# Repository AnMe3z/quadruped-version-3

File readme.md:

# Мобилен робот с безжично управление
## _MECHKA v3_

Целта на дипломната работа е да се създаде четирикрак робот с безжично управление.

Дипломант:     Андрей Методиев Ежков 12Г Випуск 2024

Ръководител: Владимир Иванов

В текущата репозитория е разделена на:

- hardware/ - четежи, CAD файлове и рендери
- software/ - сорс код на изработката

## hardware/

Тук се намират всички чертежи по корпуса, CAD файлове, рендери и файловете за платката:

- body/
- leg/
- motor/
- schematics/

Както и 3Д рендер на цялостния робот

## software/

Тук се намира сорс кода на проекта

- main/
- main.c
- control-app/
- app.c

main.c е софтуерът за микроконтролера. Инструкции за флашване:

```sh
cd software/main/build
chmod +x upload.sh
./upload.sh
```

app.py е GUI-то за контрол върху робота. Инструкции:

```sh
cd software/control-app/
source venv/bin/activate
python3 app.py
```

## License

Copyright 2023-2024 All rights reserved
Андрей Ежков си запазва всички права

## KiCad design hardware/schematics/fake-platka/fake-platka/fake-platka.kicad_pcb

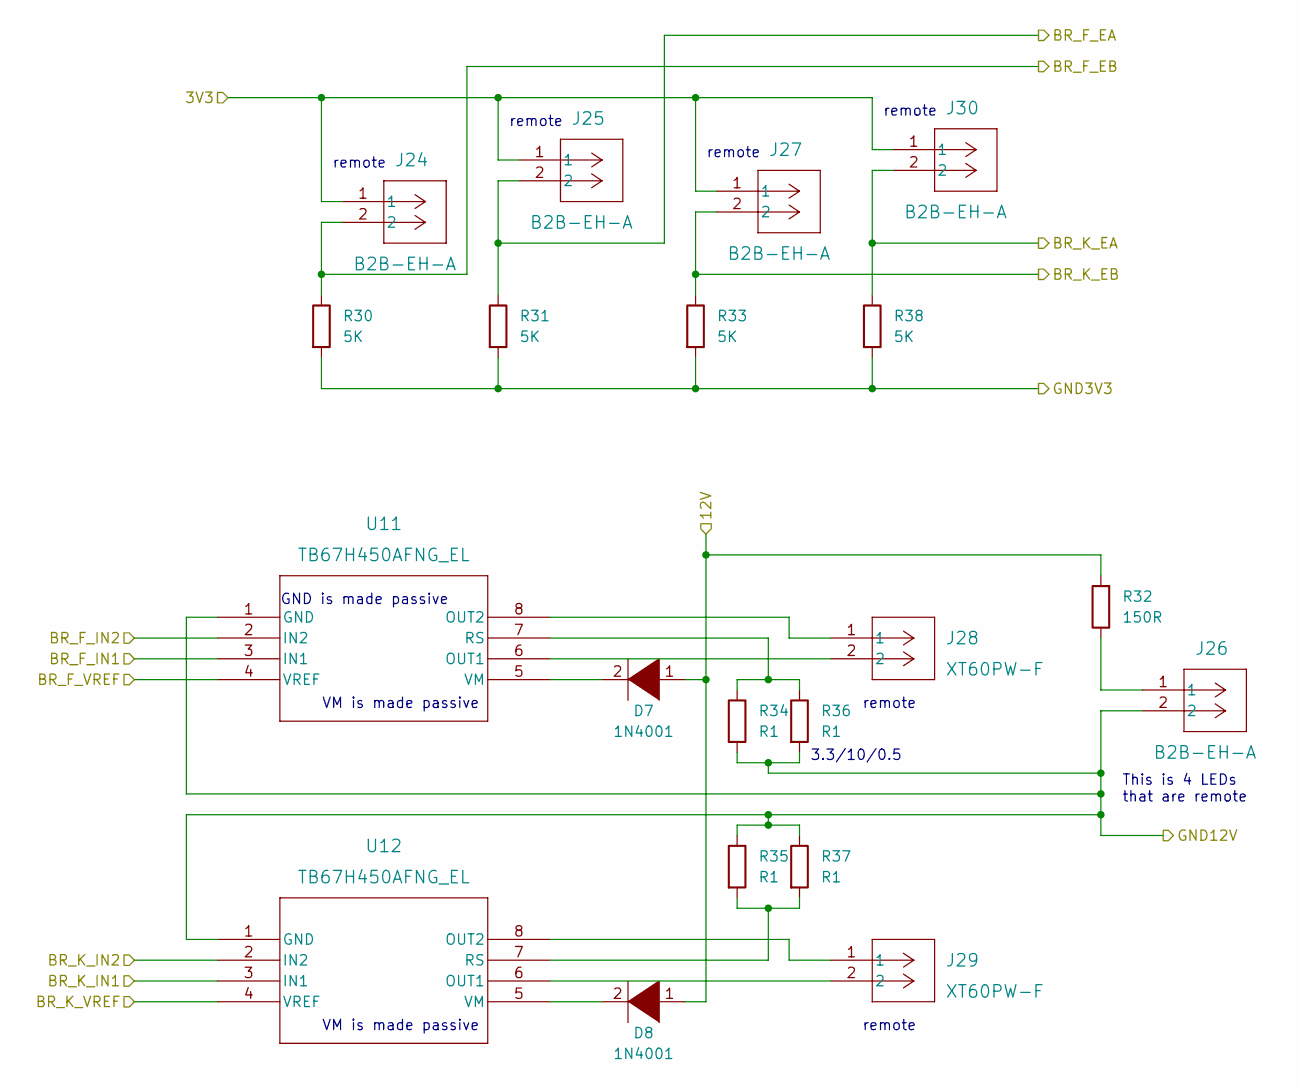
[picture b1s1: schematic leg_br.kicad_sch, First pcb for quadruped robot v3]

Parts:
D7, D8: 1N4001; D_DO-41_SOD81_P7.62mm_Horizontal
J24, J25, J26, J27, J30: B2B-EH-A; CONN_B2B-EH-A LFSN_JST
J28, J29: XT60PW-F; CONN_XT60PW-F_AMA
R30, R31, R33, R38: 5K; R_Axial_DIN0207_L6.3mm_D2.5mm_P10.16mm_Horizontal
R32: 150R; R_Axial_DIN0207_L6.3mm_D2.5mm_P10.16mm_Horizontal
R34, R35, R36, R37: R1; R_Axial_DIN0207_L6.3mm_D2.5mm_P10.16mm_Horizontal
U11, U12: TB67H450AFNG_EL; P-HSOP8-0405-1.27-002_TOS

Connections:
/Left Controller /3V3: J24.1, J25.1, J27.1, J30.1; also elsewhere on the board
/Left Controller /GND3V3: R30.2, R31.2, R33.2, R38.2; also elsewhere on the board
/Leg Back Left/12V: D7.1 (K), D8.1 (K), R32.2; also elsewhere on the board
/Leg Back Right/BR_F_EA: J25.2, R31.1; also elsewhere on the board
/Leg Back Right/BR_F_EB: J24.2, R30.1; also elsewhere on the board
/Leg Back Right/BR_F_IN1: U11.3 (IN1); also elsewhere on the board
/Leg Back Right/BR_F_IN2: U11.2 (IN2); also elsewhere on the board
/Leg Back Right/BR_F_VREF: U11.4 (VREF), U12.4 (VREF); also elsewhere on the board
/Leg Back Right/BR_K_EA: J30.2, R38.1; also elsewhere on the board
/Leg Back Right/BR_K_EB: J27.2, R33.1; also elsewhere on the board
/Leg Back Right/BR_K_IN1: U12.3 (IN1); also elsewhere on the board
/Leg Back Right/BR_K_IN2: U12.2 (IN2); also elsewhere on the board
/Leg Back Right/GND12V: J26.2, R34.2, R35.1, R36.2, R37.1, U11.1 (GND), U12.1 (GND); also elsewhere on the board
unnamed: D7.2 (A), U11.5 (VM)
unnamed: D8.2 (A), U12.5 (VM)
unnamed: J26.1, R32.1
unnamed: J28.1, U11.8 (OUT2)
unnamed: J28.2, U11.6 (OUT1)
unnamed: J29.1, U12.8 (OUT2)
unnamed: J29.2, U12.6 (OUT1)
unnamed: R34.1, R36.1, U11.7 (RS)
unnamed: R35.2, R37.2, U12.7 (RS)

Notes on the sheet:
GND is made passive
remote
This is 4 LEDs that are remote
VM is made passive
3.3/10/0.5

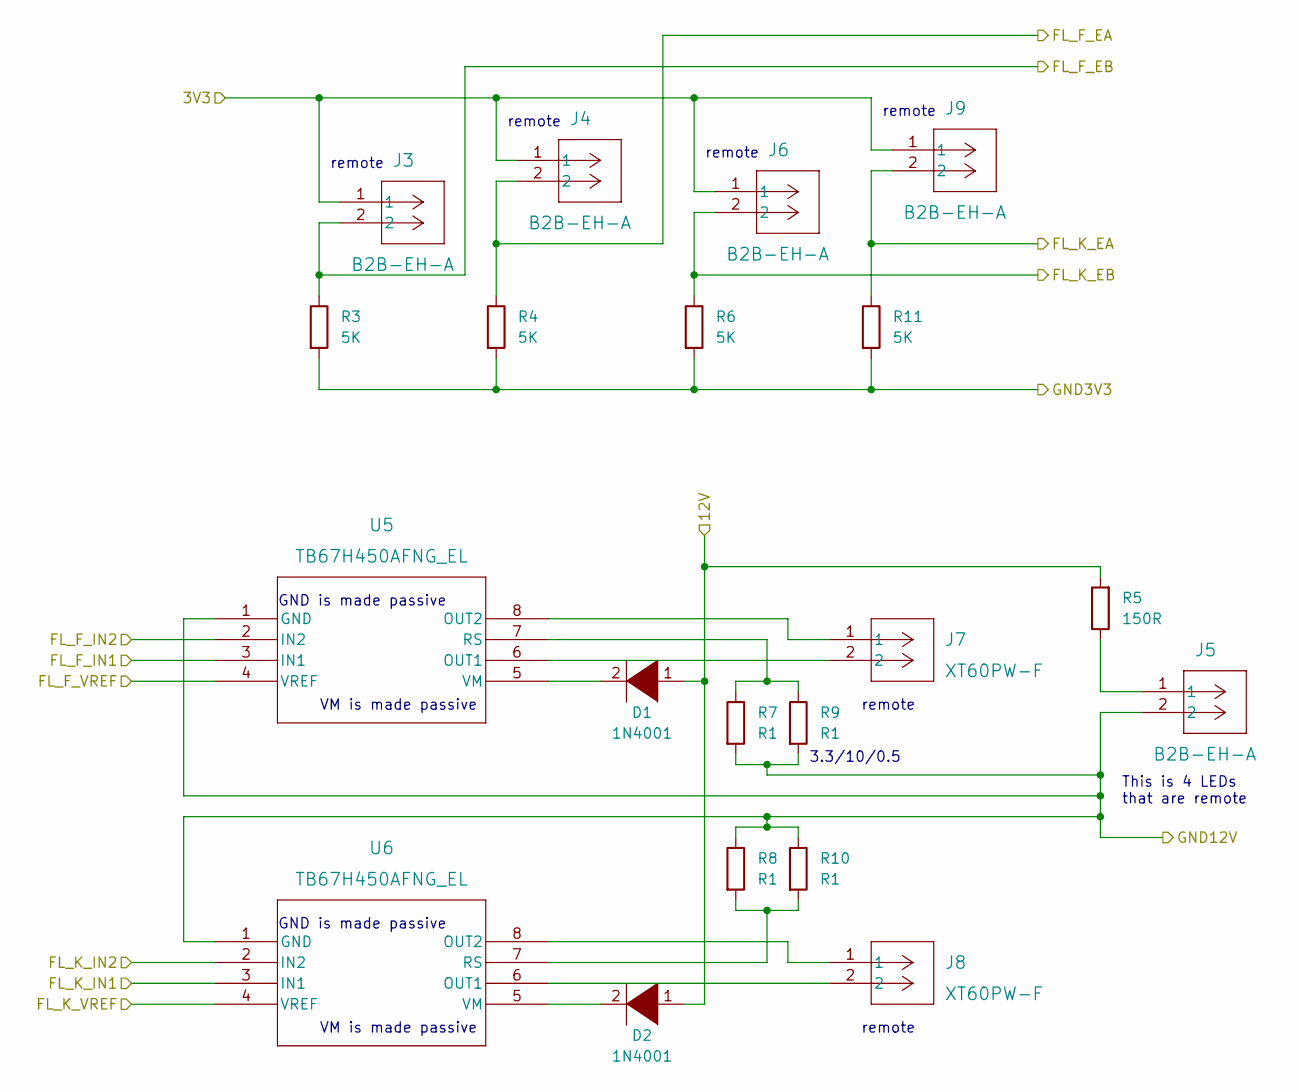
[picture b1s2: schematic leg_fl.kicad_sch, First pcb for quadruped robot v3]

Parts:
D1, D2: 1N4001; D_DO-41_SOD81_P7.62mm_Horizontal
J3, J4, J5, J6, J9: B2B-EH-A; CONN_B2B-EH-A LFSN_JST
J7, J8: XT60PW-F; CONN_XT60PW-F_AMA
R3, R4, R6, R11: 5K; R_Axial_DIN0207_L6.3mm_D2.5mm_P10.16mm_Horizontal
R5: 150R; R_Axial_DIN0207_L6.3mm_D2.5mm_P10.16mm_Horizontal
R7, R8, R9, R10: R1; R_Axial_DIN0207_L6.3mm_D2.5mm_P10.16mm_Horizontal
U5, U6: TB67H450AFNG_EL; P-HSOP8-0405-1.27-002_TOS

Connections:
/Left Controller /3V3: J3.1, J4.1, J6.1, J9.1; also elsewhere on the board
/Left Controller /3V3_VREF: U5.4 (VREF), U6.4 (VREF); also elsewhere on the board
/Left Controller /FL_F_EA: J4.2, R4.1; also elsewhere on the board
/Left Controller /FL_F_EB: J3.2, R3.1; also elsewhere on the board
/Left Controller /FL_F_IN1: U5.3 (IN1); also elsewhere on the board
/Left Controller /FL_F_IN2: U5.2 (IN2); also elsewhere on the board
/Left Controller /FL_K_EA: J9.2, R11.1; also elsewhere on the board
/Left Controller /FL_K_EB: J6.2, R6.1; also elsewhere on the board
/Left Controller /FL_K_IN1: U6.3 (IN1); also elsewhere on the board
/Left Controller /FL_K_IN2: U6.2 (IN2); also elsewhere on the board
/Left Controller /GND3V3: R3.2, R4.2, R6.2, R11.2; also elsewhere on the board
/Leg Back Left/12V: D1.1 (K), D2.1 (K), J5.2, R5.2, R7.2, R8.1, R9.2, R10.1, U5.1 (GND), U6.1 (GND); also elsewhere on the board
unnamed: D1.2 (A), U5.5 (VM)
unnamed: D2.2 (A), U6.5 (VM)
unnamed: J5.1, R5.1
unnamed: J7.1, U5.8 (OUT2)
unnamed: J7.2, U5.6 (OUT1)
unnamed: J8.1, U6.8 (OUT2)
unnamed: J8.2, U6.6 (OUT1)
unnamed: R7.1, R9.1, U5.7 (RS)
unnamed: R8.2, R10.2, U6.7 (RS)

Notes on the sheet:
remote
VM is made passive
GND is made passive
This is 4 LEDs that are remote
3.3/10/0.5

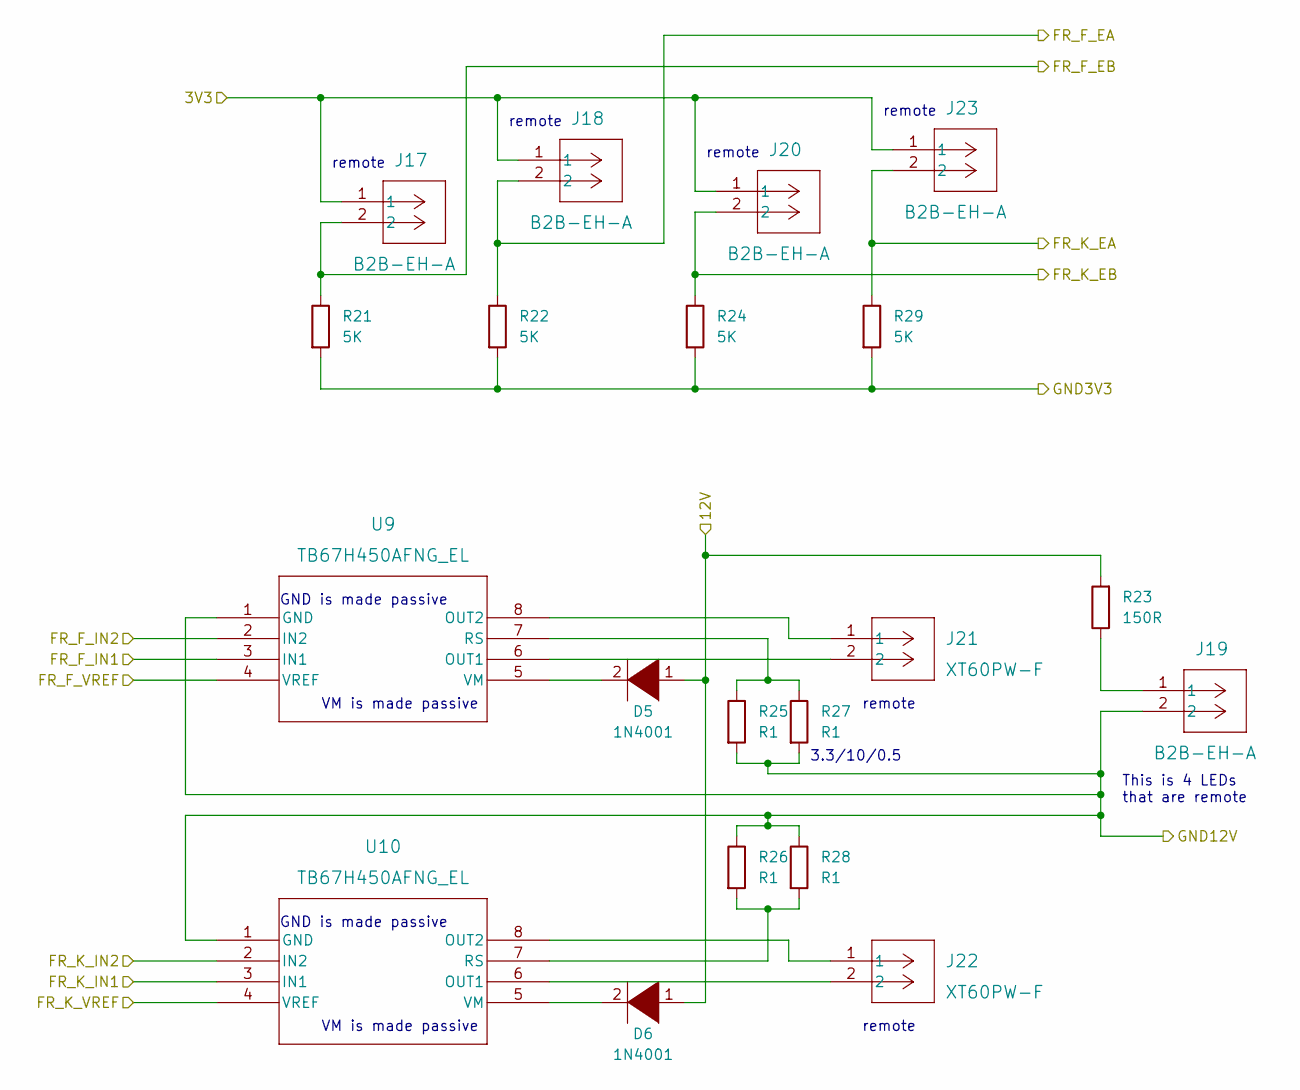
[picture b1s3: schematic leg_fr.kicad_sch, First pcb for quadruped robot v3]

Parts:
D5, D6: 1N4001; D_DO-41_SOD81_P7.62mm_Horizontal
J17, J18, J19, J20, J23: B2B-EH-A; CONN_B2B-EH-A LFSN_JST
J21, J22: XT60PW-F; CONN_XT60PW-F_AMA
R21, R22, R24, R29: 5K; R_Axial_DIN0207_L6.3mm_D2.5mm_P10.16mm_Horizontal
R23: 150R; R_Axial_DIN0207_L6.3mm_D2.5mm_P10.16mm_Horizontal
R25, R26, R27, R28: R1; R_Axial_DIN0207_L6.3mm_D2.5mm_P10.16mm_Horizontal
U9, U10: TB67H450AFNG_EL; P-HSOP8-0405-1.27-002_TOS

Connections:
/Left Controller /3V3: J17.1, J18.1, J20.1, J23.1; also elsewhere on the board
/Left Controller /GND3V3: R21.2, R22.2, R24.2, R29.2; also elsewhere on the board
/Leg Back Left/12V: D5.1 (K), D6.1 (K), R23.2; also elsewhere on the board
/Leg Back Right/BR_F_VREF: U9.4 (VREF), U10.4 (VREF); also elsewhere on the board
/Leg Back Right/GND12V: J19.2, R25.2, R26.1, R27.2, R28.1, U9.1 (GND), U10.1 (GND); also elsewhere on the board
/Leg Front Right/FR_F_EA: J18.2, R22.1; also elsewhere on the board
/Leg Front Right/FR_F_EB: J17.2, R21.1; also elsewhere on the board
/Leg Front Right/FR_F_IN1: U9.3 (IN1); also elsewhere on the board
/Leg Front Right/FR_F_IN2: U9.2 (IN2); also elsewhere on the board
/Leg Front Right/FR_K_EA: J23.2, R29.1; also elsewhere on the board
/Leg Front Right/FR_K_EB: J20.2, R24.1; also elsewhere on the board
/Leg Front Right/FR_K_IN1: U10.3 (IN1); also elsewhere on the board
/Leg Front Right/FR_K_IN2: U10.2 (IN2); also elsewhere on the board
unnamed: D5.2 (A), U9.5 (VM)
unnamed: D6.2 (A), U10.5 (VM)
unnamed: J21.1, U9.8 (OUT2)
unnamed: J21.2, U9.6 (OUT1)
unnamed: J22.1, U10.8 (OUT2)
unnamed: J22.2, U10.6 (OUT1)
unnamed: J19.1, R23.1
unnamed: R25.1, R27.1, U9.7 (RS)
unnamed: R26.2, R28.2, U10.7 (RS)

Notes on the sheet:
This is 4 LEDs that are remote
GND is made passive
3.3/10/0.5
remote
VM is made passive

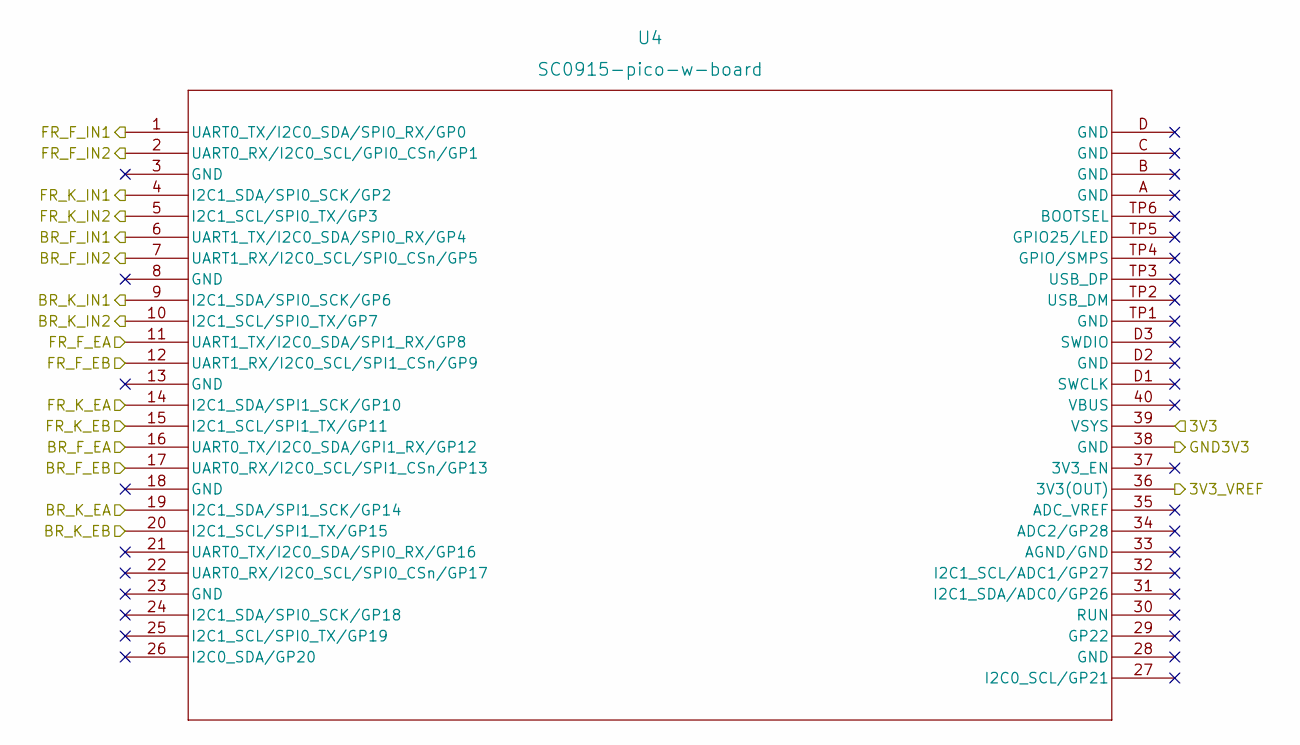
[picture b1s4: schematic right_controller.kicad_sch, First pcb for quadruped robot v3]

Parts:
U4: SC0915-pico-w-board; RPi_PicoW_SMD_TH

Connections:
/Left Controller /3V3: U4.39 (VSYS); also elsewhere on the board
/Left Controller /GND3V3: U4.38 (GND); also elsewhere on the board
/Leg Back Right/BR_F_EA: U4.16 (UART0_TX/I2C0_SDA/GPI1_RX/GP12); also elsewhere on the board
/Leg Back Right/BR_F_EB: U4.17 (UART0_RX/I2C0_SCL/SPI1_CSn/GP13); also elsewhere on the board
/Leg Back Right/BR_F_IN1: U4.6 (UART1_TX/I2C0_SDA/SPI0_RX/GP4); also elsewhere on the board
/Leg Back Right/BR_F_IN2: U4.7 (UART1_RX/I2C0_SCL/SPI0_CSn/GP5); also elsewhere on the board
/Leg Back Right/BR_F_VREF: U4.36 (3V3(OUT)); also elsewhere on the board
/Leg Back Right/BR_K_EA: U4.19 (I2C1_SDA/SPI1_SCK/GP14); also elsewhere on the board
/Leg Back Right/BR_K_EB: U4.20 (I2C1_SCL/SPI1_TX/GP15); also elsewhere on the board
/Leg Back Right/BR_K_IN1: U4.9 (I2C1_SDA/SPI0_SCK/GP6); also elsewhere on the board
/Leg Back Right/BR_K_IN2: U4.10 (I2C1_SCL/SPI0_TX/GP7); also elsewhere on the board
/Leg Front Right/FR_F_EA: U4.11 (UART1_TX/I2C0_SDA/SPI1_RX/GP8); also elsewhere on the board
/Leg Front Right/FR_F_EB: U4.12 (UART1_RX/I2C0_SCL/SPI1_CSn/GP9); also elsewhere on the board
/Leg Front Right/FR_F_IN1: U4.1 (UART0_TX/I2C0_SDA/SPI0_RX/GP0); also elsewhere on the board
/Leg Front Right/FR_F_IN2: U4.2 (UART0_RX/I2C0_SCL/GPI0_CSn/GP1); also elsewhere on the board
/Leg Front Right/FR_K_EA: U4.14 (I2C1_SDA/SPI1_SCK/GP10); also elsewhere on the board
/Leg Front Right/FR_K_EB: U4.15 (I2C1_SCL/SPI1_TX/GP11); also elsewhere on the board
/Leg Front Right/FR_K_IN1: U4.4 (I2C1_SDA/SPI0_SCK/GP2); also elsewhere on the board
/Leg Front Right/FR_K_IN2: U4.5 (I2C1_SCL/SPI0_TX/GP3); also elsewhere on the board

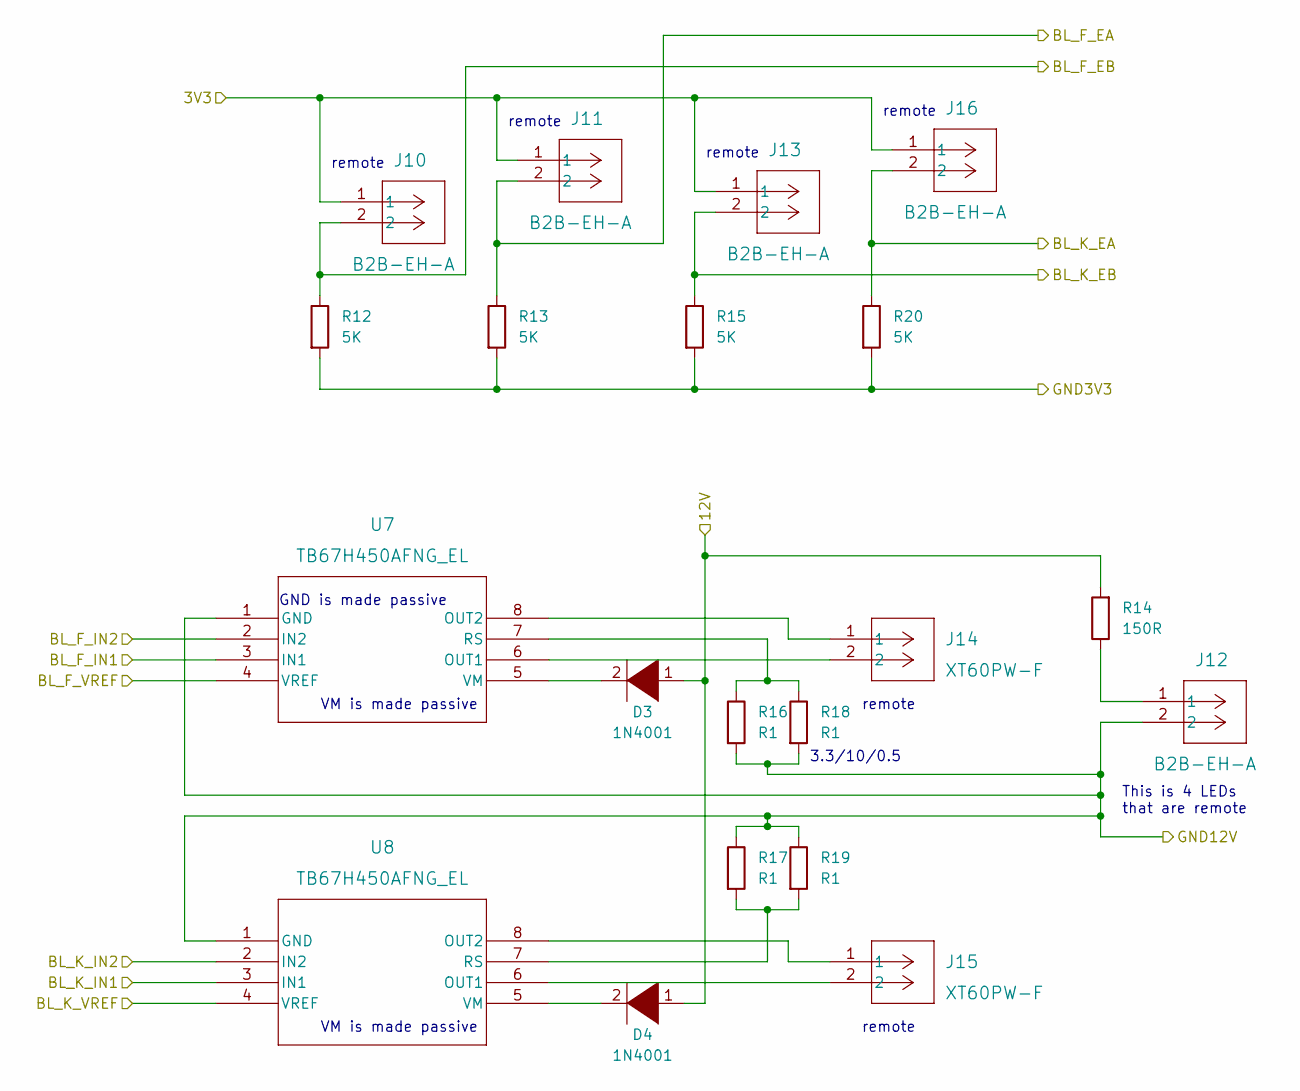
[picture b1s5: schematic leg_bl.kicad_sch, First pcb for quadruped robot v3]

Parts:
D3, D4: 1N4001; D_DO-41_SOD81_P7.62mm_Horizontal
J10, J11, J12, J13, J16: B2B-EH-A; CONN_B2B-EH-A LFSN_JST
J14, J15: XT60PW-F; CONN_XT60PW-F_AMA
R12, R13, R15, R20: 5K; R_Axial_DIN0207_L6.3mm_D2.5mm_P10.16mm_Horizontal
R14: 150R; R_Axial_DIN0207_L6.3mm_D2.5mm_P10.16mm_Horizontal
R16, R17, R18, R19: R1; R_Axial_DIN0207_L6.3mm_D2.5mm_P10.16mm_Horizontal
U7, U8: TB67H450AFNG_EL; P-HSOP8-0405-1.27-002_TOS

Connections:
/Left Controller /3V3: J10.1, J11.1, J13.1, J16.1; also elsewhere on the board
/Left Controller /3V3_VREF: U7.4 (VREF), U8.4 (VREF); also elsewhere on the board
/Left Controller /BL_F_EA: J11.2, R13.1; also elsewhere on the board
/Left Controller /BL_F_EB: J10.2, R12.1; also elsewhere on the board
/Left Controller /BL_F_IN1: U7.3 (IN1); also elsewhere on the board
/Left Controller /BL_F_IN2: U7.2 (IN2); also elsewhere on the board
/Left Controller /BL_K_EA: J16.2, R20.1; also elsewhere on the board
/Left Controller /BL_K_EB: J13.2, R15.1; also elsewhere on the board
/Left Controller /BL_K_IN1: U8.3 (IN1); also elsewhere on the board
/Left Controller /BL_K_IN2: U8.2 (IN2); also elsewhere on the board
/Left Controller /GND3V3: R12.2, R13.2, R15.2, R20.2; also elsewhere on the board
/Leg Back Left/12V: D3.1 (K), D4.1 (K), J12.2, R14.2, R16.2, R17.1, R18.2, R19.1, U7.1 (GND), U8.1 (GND); also elsewhere on the board
unnamed: D3.2 (A), U7.5 (VM)
unnamed: D4.2 (A), U8.5 (VM)
unnamed: J14.1, U7.8 (OUT2)
unnamed: J14.2, U7.6 (OUT1)
unnamed: J15.1, U8.8 (OUT2)
unnamed: J15.2, U8.6 (OUT1)
unnamed: J12.1, R14.1
unnamed: R16.1, R18.1, U7.7 (RS)
unnamed: R17.2, R19.2, U8.7 (RS)

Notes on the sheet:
remote
VM is made passive
GND is made passive
3.3/10/0.5
This is 4 LEDs that are remote

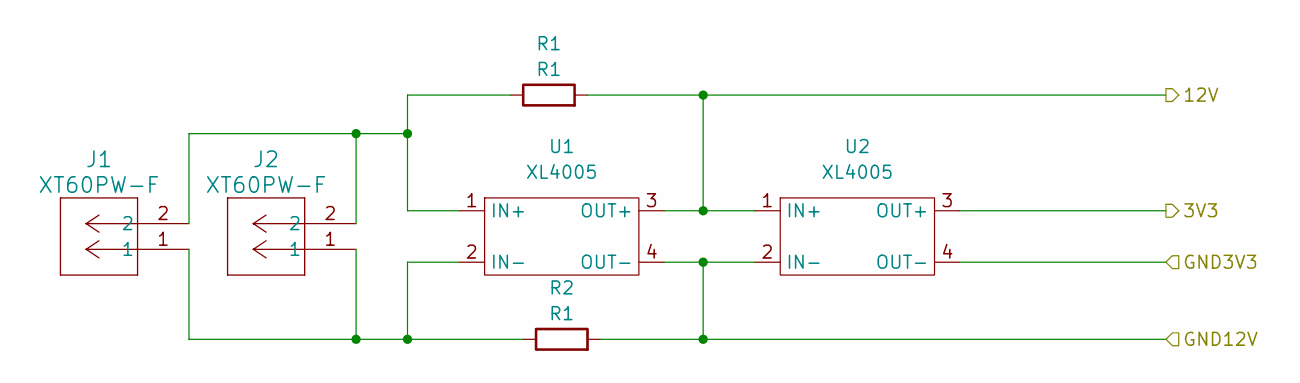
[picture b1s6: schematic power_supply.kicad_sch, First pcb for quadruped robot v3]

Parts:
J1, J2: XT60PW-F; CONN_XT60PW-F_AMA
R1, R2: R1; R_Axial_DIN0207_L6.3mm_D2.5mm_P10.16mm_Horizontal
U1, U2: XL4005; XL4005_DC-DC

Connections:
/Left Controller /3V3: U2.3 (OUT+); also elsewhere on the board
/Left Controller /GND3V3: U2.4 (OUT-); also elsewhere on the board
/Leg Back Left/12V: R1.2, U1.3 (OUT+), U2.1 (IN+); also elsewhere on the board
/Leg Back Right/GND12V: R2.2, U1.4 (OUT-), U2.2 (IN-); also elsewhere on the board
unnamed: J1.1, J2.1, R2.1, U1.2 (IN-)
unnamed: J1.2, J2.2, R1.1, U1.1 (IN+)

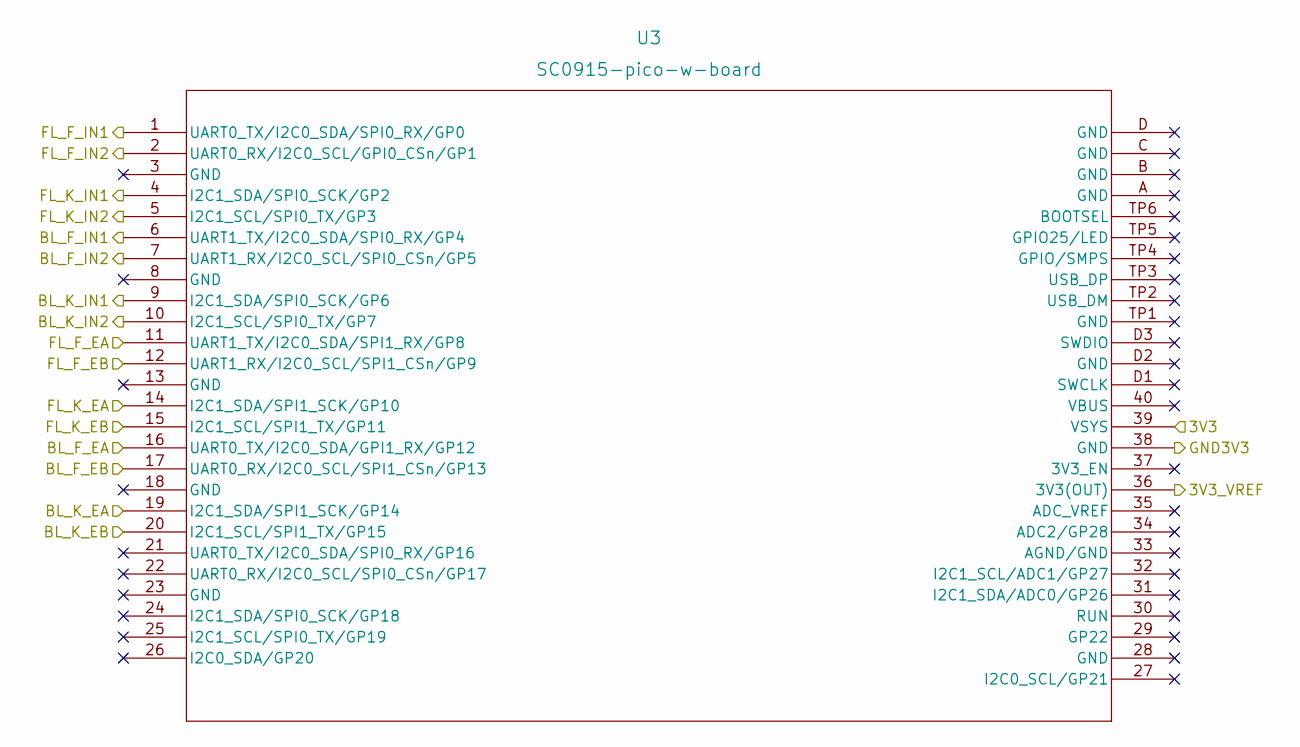
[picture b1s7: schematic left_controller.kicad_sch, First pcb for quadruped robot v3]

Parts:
U3: SC0915-pico-w-board; RPi_PicoW_SMD_TH

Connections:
/Left Controller /3V3: U3.39 (VSYS); also elsewhere on the board
/Left Controller /3V3_VREF: U3.36 (3V3(OUT)); also elsewhere on the board
/Left Controller /BL_F_EA: U3.16 (UART0_TX/I2C0_SDA/GPI1_RX/GP12); also elsewhere on the board
/Left Controller /BL_F_EB: U3.17 (UART0_RX/I2C0_SCL/SPI1_CSn/GP13); also elsewhere on the board
/Left Controller /BL_F_IN1: U3.6 (UART1_TX/I2C0_SDA/SPI0_RX/GP4); also elsewhere on the board
/Left Controller /BL_F_IN2: U3.7 (UART1_RX/I2C0_SCL/SPI0_CSn/GP5); also elsewhere on the board
/Left Controller /BL_K_EA: U3.19 (I2C1_SDA/SPI1_SCK/GP14); also elsewhere on the board
/Left Controller /BL_K_EB: U3.20 (I2C1_SCL/SPI1_TX/GP15); also elsewhere on the board
/Left Controller /BL_K_IN1: U3.9 (I2C1_SDA/SPI0_SCK/GP6); also elsewhere on the board
/Left Controller /BL_K_IN2: U3.10 (I2C1_SCL/SPI0_TX/GP7); also elsewhere on the board
/Left Controller /FL_F_EA: U3.11 (UART1_TX/I2C0_SDA/SPI1_RX/GP8); also elsewhere on the board
/Left Controller /FL_F_EB: U3.12 (UART1_RX/I2C0_SCL/SPI1_CSn/GP9); also elsewhere on the board
/Left Controller /FL_F_IN1: U3.1 (UART0_TX/I2C0_SDA/SPI0_RX/GP0); also elsewhere on the board
/Left Controller /FL_F_IN2: U3.2 (UART0_RX/I2C0_SCL/GPI0_CSn/GP1); also elsewhere on the board
/Left Controller /FL_K_EA: U3.14 (I2C1_SDA/SPI1_SCK/GP10); also elsewhere on the board
/Left Controller /FL_K_EB: U3.15 (I2C1_SCL/SPI1_TX/GP11); also elsewhere on the board
/Left Controller /FL_K_IN1: U3.4 (I2C1_SDA/SPI0_SCK/GP2); also elsewhere on the board
/Left Controller /FL_K_IN2: U3.5 (I2C1_SCL/SPI0_TX/GP3); also elsewhere on the board
/Left Controller /GND3V3: U3.38 (GND); also elsewhere on the board

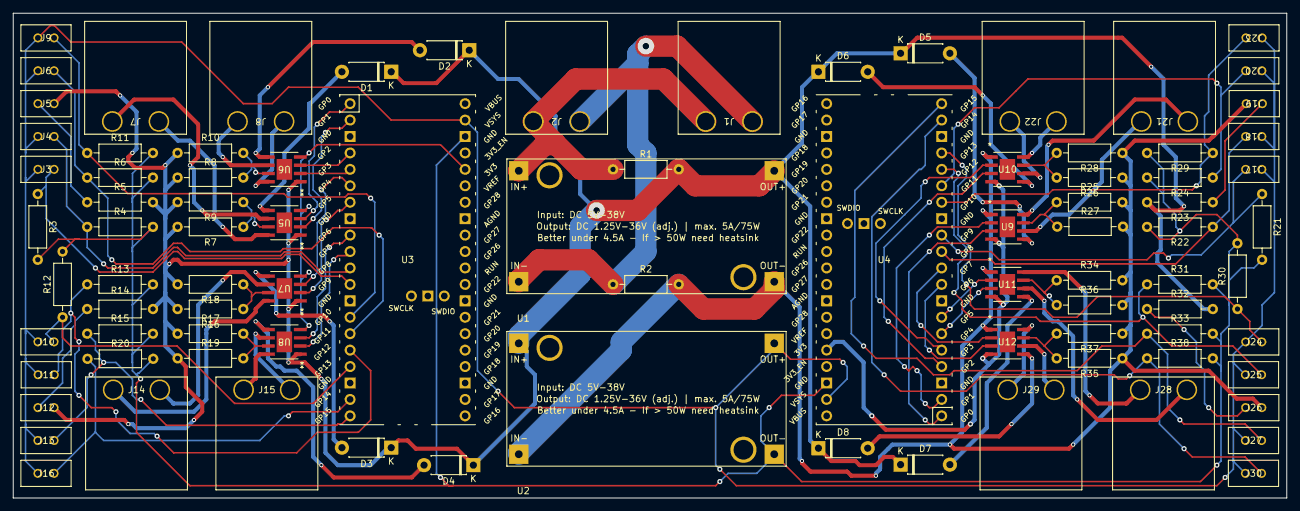
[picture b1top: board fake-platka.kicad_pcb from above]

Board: 2 copper layers, 196.9 x 74.9 mm, 88 parts (0 on the bottom side), 76 nets.

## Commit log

2023-10-03 added motor model
2023-10-04 added razhodi
2023-10-06 working on the hip
2023-10-06 working on hip lower
2023-10-07 working on the hip reworked
2023-10-07 finished hip-lower
2023-10-10 added knee
2023-10-10 added femur
2023-10-10 reworked leg and motor renders
2023-10-10 added knee drive
2023-10-12 progress
2023-10-18 finished updated femur and knee redisign
2023-10-26 added encoder base body
2023-11-23 have been working on the driver
2023-11-23 added pwm software
2023-11-23 added user input duty cycle
2023-11-25 added second PWM
2023-11-25 added high level motor control function
2023-12-06 backup
2023-12-09 added led pwm control
2023-12-09 added phototransistor read program
2023-12-13 added single encoder
2023-12-17 added single encoder servo code
2023-12-22 improved encoder design
2023-12-23 refining the encoder wheel and hip cap
2023-12-26 added quadrature encoder software
2023-12-26 added self made quadrature software for positioning
2023-12-26 working quadrature encoder for position
2023-12-27 trying to confine quadrature encoder to one sm
2023-12-28 daily backup
2023-12-28 reorganized the repo
2023-12-28 new knee design
2023-12-28 returned old knee and redesigned hip lower
2024-01-02 started writing leg controller code (currently not working)
2024-01-03 working motor 2 control
2024-01-04 working on new femur
2024-01-04 finished the new femur
2024-01-09 added P control (not entirely tested)
2024-01-10 working P control
2024-01-11 encoder and p control
2024-01-15 pwm interrupt
2024-01-15 cat servo inner loop pwm interrupt (untested)
2024-01-16 figuring out the pwm interrupt
2024-01-16 somehow wokring with suspect P mapping to PWM
2024-01-17 working pwm irq control loop
2024-01-17 cleaned the pwm irq control loop
2024-01-17 double motor inner control loop
2024-01-18 measured pwd irq freq and execution time for irq func
2024-01-18 fixed pwm irq reinit bug
2024-01-19 some questionable hole counting (doesn not work)
2024-01-19 working reverse inner loop servo control in debug mode
2024-01-19 working reverse inner loop servo control @ 10kHz
2024-01-21 added encoder maxmin position check
2024-01-21 added femur encoder shell
2024-01-25 separated control loop obligations
2024-01-26 redowing the knee movement mechanism
2024-01-27 redesigning leg
2024-01-29 refing the new leg design
2024-01-30 almost done with the redesign
2024-01-30 finalizing the design
2024-02-02 more refinement
2024-02-03 non-stop design renfinement'
2024-02-03 femur finished
2024-02-04 fucking encodr works again (returned to metal foil)
2024-02-04 started working on the mandatory pcb
2024-02-05 starting to write the documentation
2024-02-05 made first pcb
2024-02-06 added all components to the schematic and pcb
2024-02-09 working on pcb and documentation
2024-02-12 board finished
2024-02-14 finalizing the documentation
2024-02-15 added experimental encoder masks
2024-02-17 finished hip upper
2024-02-17 added body mounts
2024-02-18 added side lower
2024-02-18 added side upper
2024-02-18 added parallel
2024-02-18 added space for hip encoder cap and reallocated some m3 holes
2024-02-26 mutliple days of progress; documentation done; minor part adjustments
2024-02-26 minor adjustments
2024-03-06 sync
2024-03-06 working driver control on the new board
2024-03-07 working quadrature signal
2024-03-07 working pio encoder
2024-03-07 added encoder infrastructure
2024-03-07 added pos var reset and pio Y count reset
2024-03-07 added P control
2024-03-07 added P control infrastructure
2024-03-18 fixed dimensions of the knee drive
2024-03-18 body work
2024-04-03 added timer irq
2024-04-04 CODE BROKEN started to rework the code, reallocating the encoder counting from pio to pwm irq
2024-04-05 reworked the encoder reading
2024-04-07 working udp beacon
2024-04-07 working receiving udp code
2024-04-07 working udp code with commands
2024-04-08 added full upd control into the main code
2024-04-10 working 2 sided main control
2024-04-16 ssoftware working so far
2024-04-16 added axis slit count
2024-04-16 added debug struct
2024-04-19 started working on the control app
2024-04-19 slider control on 4 legs
2024-04-20 added message generator
2024-04-20 added stand alone message generator
2024-04-20 completed stand alone message generator
2024-04-20 added message generator to the leg simulator
2024-04-28 working on the control app
2024-04-28 finished the basic message generator
2024-04-28 added q and command sequencing
2024-05-03 adjusted leg behaviour
2024-05-03 added inverse kinematics
2024-05-03 adjustments ik
2024-05-03 reorganized variable handling; added pitch
2024-05-03 fixed the sequencing
2024-05-07 added x pivot
2024-05-07 added invertion of the message, 0.25 incr. x and p sliders
2024-05-07 reworked the graph leg movement
2024-05-07 fixed ik
2024-05-07 fixed x piv
2024-05-07 fixed pitch
2024-05-07 fixed message generation
2024-05-09 fixed pitch leg addressation
2024-05-09 queue consider functionality
2024-05-10 added x pivot for only front axle
2024-05-13 raznishtih polling mode; turned on
2024-05-13 added polling in main; optimized code
2024-05-14 removed the polling delay
2024-05-14 added safety margin
2024-05-18 added editable seq sender
2024-05-20 cleaned
2024-05-20 polished the repo
2024-05-20 added readme.md
